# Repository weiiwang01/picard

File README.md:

# PiCard

> [!IMPORTANT]  
> PiCard is currently under development.

PiCard is a miniaturized Raspberry Pi Compute Module carrier board optimized for Linux server use cases.

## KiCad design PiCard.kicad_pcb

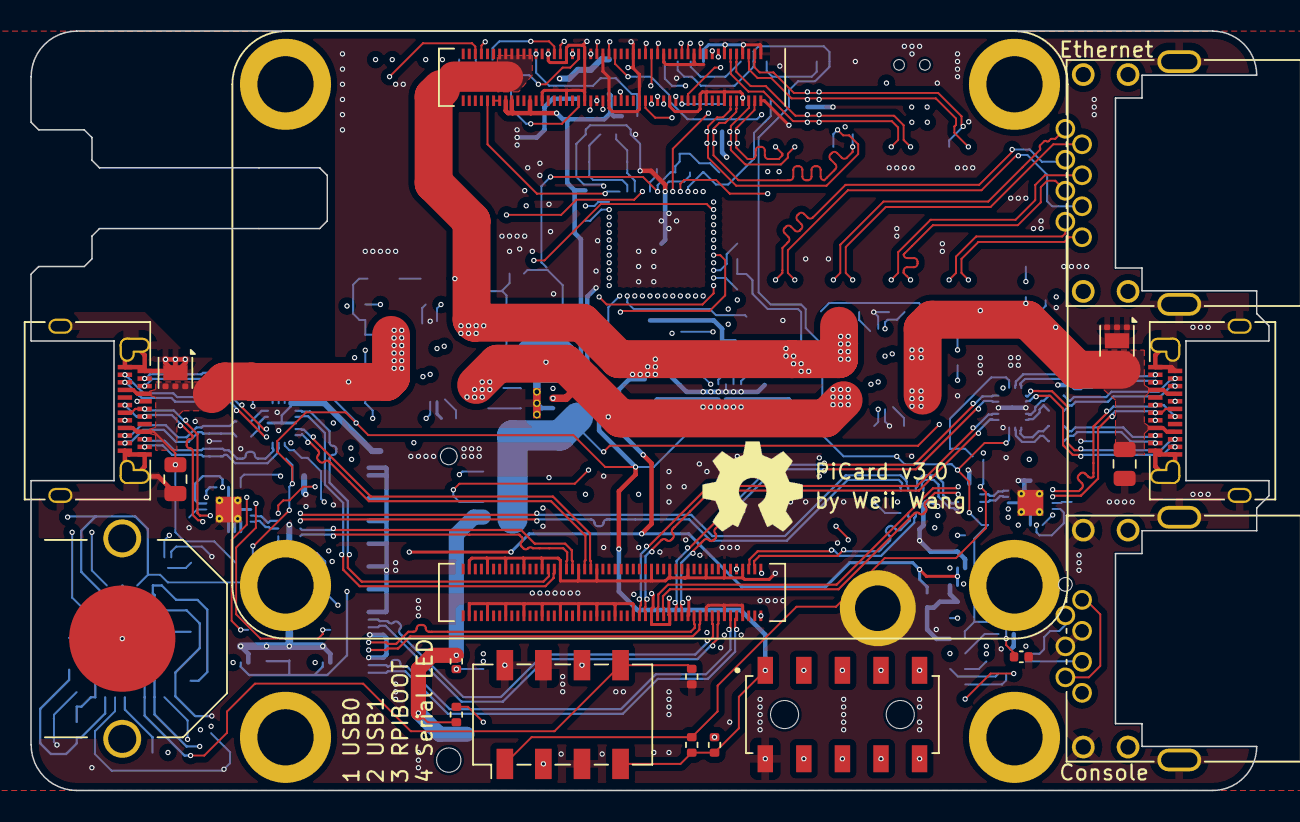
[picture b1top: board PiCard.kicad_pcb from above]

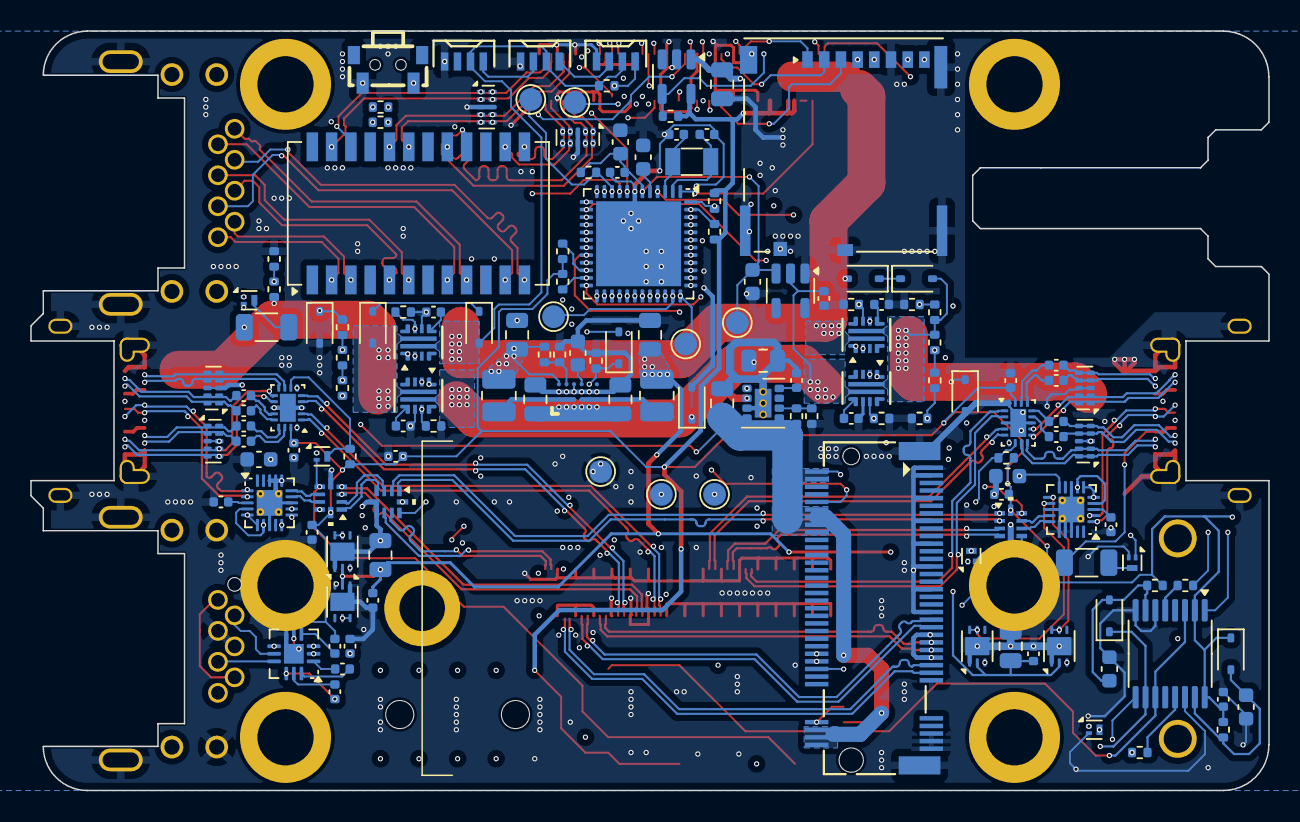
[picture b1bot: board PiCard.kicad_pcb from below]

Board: 6 copper layers, 81.5 x 50.0 mm, 166 parts (145 on the bottom side), 201 nets.

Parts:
BT1: CR1220 Battery; BAT-SMD_MY-1220-03
C1, C2, C3, C4, C5, C17, C21, C27, C28, C29, C30, C31, C32, C33, C34, C35, C36, C37, C38, C39, C40, C41, C43, C46, C51: 100n; C_0402_1005Metric
C6, C7, C25, C26, C44, C47: 1u; C_0603_1608Metric
C8, C18, C22: 10u; C_0805_2012Metric
C9, C10, C13, C14: 22u; C_0805_2012Metric
C11, C12: 47u; C_0805_2012Metric
C15: 22n; C_0603_1608Metric
C16: 430pF; C_0402_1005Metric
C19, C20, C23, C24: 2.2n; C_0402_1005Metric
C42: 4.7u; C_0603_1608Metric
C45, C48: 18pf; C_0402_1005Metric
C49, C50: 4.7u 50V; C_0805_2012Metric
ComputeModule1: ComputeModule4-CM4; Raspberry-Pi-4-Compute-Module
D1, D2, D3, D8, D9: 1N5819WS; D_SOD-323
D4, D7: Zener 20V; D_SOD-323
D5, D6, D13: D; D_SOD-323
D10, D11, D12: WS2812B; LED-SMD_4P-L4.0-W1.7-R
H1, H2: MountingHole; MOUNTING-HOLE
J1: RS232; RJ45-TH_RJ45-005-202-11
J2: Ethernet; RJ45-TH_RJ45-005-202-11
J3: Micro_SD_Card_Det2; SDCARD_MOLEX_503398-1892
J4: Bus_M.2_Socket_M; CONN-SMD_APCI0146-P001A
J5, J6: USB_C_Receptacle; USB-C-SMD_TYPE-C-31-M-27
J7: Conn_02x05_Odd_Even; HARWIN_M20-7810545R
L1, L2: 1u; L_1008_2520Metric
Q1, Q2, Q3, Q4, Q5: DMN32D2LFB4; Diodes_DFN1006-3
R1, R2, R5, R6: 470; R_0402_1005Metric
R3, R4, R12: 100k 1%; R_0402_1005Metric
R7, R8, R14, R25, R26, R39, R40, R41: 12k; R_0402_1005Metric
R9, R34, R35, R37, R38: 3.3k; R_0402_1005Metric
R10: 787k; R_0402_1005Metric
R11: 309k; R_0402_1005Metric
R13: 150k 1%; R_0402_1005Metric
R15, R16: 220k 1%; R_0402_1005Metric
R17, R18: 59k; R_0402_1005Metric
R19, R20: 28.7k; R_0402_1005Metric
R21, R22, R23, R24: 953; R_0402_1005Metric
R27, R28: 120k; R_0402_1005Metric
R29, R30: 4.7k 0.25W; R_1206_3216Metric
R31, R32: 10k; R_0402_1005Metric
R33, R36: 5.1k; R_0402_1005Metric
SW1: SW_Push; SW-SMD_L4.7-W3.5-P3.35-EH
SW2: SW_DIP_x04; SW-SMD_8P-L11.1-W6.2-P2.54-LS7.8
SYM1: PiCard v3.0; PICARD_NAMEPLATE
TP1, TP2, TP3, TP4, TP5, TP6, TP7, TP8: TestPoint; TestPoint_Pad_D1.5mm
TR1: H2456G; XFMR-SMD-24_L16.6-W9.0-LS9.6-BL
U1: ADM3101EACPZ; LFCSP-12-1EP_3x3mm_P0.5mm_EP1.3x1.3mm
U2: 74HC123PW; TSSOP-16_4.4x5mm_P0.65mm
U3, U4, U18, U19, U20, U21: TPD4EUSB30; USON-10_2.5x1.0mm_P0.5mm
U5: AP2191W; SOT-23-5
U6: TPS82130; Texas_SIL0008D_MicroSiP-8-1EP_2.8x3mm_P0.65mm_EP1.1x1.9mm_T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
U7: TPS62180; YZF0024AMAM
U8, U13, U14, U15: AP21510; DFN-6-1EP_2x1.8mm_P0.5mm_EP1.2x1.6mm
U9, U10: TVS2200DRV; WSON-6-1EP_2x2mm_P0.65mm_EP1x1.6mm
U11, U12, U16, U17: TPS259470; RPW0010A-MFG
U22, U23: TPD6S300A; WQFN-20-1EP_3x3mm_P0.4mm_EP1.7x1.7mm_ThermalVias
U24, U25: FUSB340TMX; QFN-18-1EP_2x2.8mm_P0.4mm_EP1.05x1.85mm
U26, U27, U28: TS3USB221; RSE10
U29: TLV70433; SOT-23-5
U30: STM32G071CBUx; QFN-48-1EP_7x7mm_P0.5mm_EP5.6x5.6mm
Y1: 32.768kHz; Crystal_SMD_3215-2Pin_3.2x1.5mm

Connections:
+3.3V: C2.1, C5.2, C29.2, C30.2, C39.2, C40.2, C41.2, C51.1, ComputeModule1.78 (GPIO_VREF(1.8v/3.3v_Input)), ComputeModule1.84 (+3.3v_(Output)), ComputeModule1.86 (+3.3v_(Output)), D1.1 (K), D2.1 (K), J2.10, J2.12, J7.1, R3.1, R4.1, R7.2, R25.1, R26.1, R34.2, R35.2, R37.2, R38.2, R39.1, R40.1, SW2.4, U1.5 (VCC), U2.2 (B), U2.10 (B), U2.16 (VCC), U5.5 (IN), U24.17 (VDD), U25.17 (VDD), U26.10 (VCC), U27.10 (VCC), U28.10 (VCC)
+5V: C11.1, C12.1, C17.1, C18.1, C21.1, C22.1, ComputeModule1.77 (+5v_(Input)), ComputeModule1.79 (+5v_(Input)), ComputeModule1.81 (+5v_(Input)), ComputeModule1.83 (+5v_(Input)), ComputeModule1.85 (+5v_(Input)), ComputeModule1.87 (+5v_(Input)), D4.2 (A), D7.2 (A), D10.2 (VDD), D11.2 (VDD), D12.2 (VDD), L1.2, L2.2, R10.1, R33.1, U7.A4 (VO), U8.2 (IN), U13.2 (IN), U14.2 (IN), U15.2 (IN), U16.5 (IN), U17.5 (IN)
/MCU/LDO_3.3V: C42.1, C43.2, C47.1, R36.2, TP4.1, U29.3 (OUT), U30.6 (VDD)
/MCU/MCU_BUTTON: SW1.2, U30.9 (PF1)
/MCU/WS2812_DIN: D10.1 (DIN), R33.2, U30.12 (PA1)
/Module A/DA_N: J2.2, TR1.8 (MX3+)
/Module A/DA_P: J2.1, TR1.9 (MX3-)
/Module A/DB_N: J2.6, TR1.11 (MX4+)
/Module A/DB_P: J2.3, TR1.12 (MX4-)
/Module A/DC_N: J2.5, TR1.5 (MX2+)
/Module A/DC_P: J2.4, TR1.6 (MX2-)
/Module A/DD_N: J2.8, TR1.2 (MX1+)
/Module A/DD_P: J2.7, TR1.3 (MX1-)
/Module A/ETH_LEDG: ComputeModule1.17 (Ethernet_nLED2(3.3v)), R5.2
/Module A/ETH_LEDY: ComputeModule1.15 (Ethernet_nLED3(3.3v)), R6.2
/Module A/GPIO14_UART_TX: ComputeModule1.55 (GPIO14), U1.3 (TIN), U2.1 (A)
/Module A/GPIO15_UART_RX: ComputeModule1.51 (GPIO15), U1.2 (ROUT), U2.9 (A)
/Module A/RS232_RXD: J1.6, U1.9 (RIN)
/Module A/RS232_TXD: J1.3, U1.8 (TOUT)
/Module A/SD_CLK: ComputeModule1.57 (SD_CLK), J3.5 (CLK)
/Module A/SD_CMD: ComputeModule1.62 (SD_CMD), J3.3 (CMD)
/Module A/SD_DAT0: ComputeModule1.63 (SD_DAT0), J3.7 (DAT0)
/Module A/SD_DAT1: ComputeModule1.67 (SD_DAT1), J3.8 (DAT1)
/Module A/SD_DAT2: ComputeModule1.69 (SD_DAT2), J3.1 (DAT2)
/Module A/SD_DAT3: ComputeModule1.61 (SD_DAT3), J3.2 (DAT3/CD)
/Module A/SD_PWR: C8.1, J3.4 (VDD), U5.1 (OUT)
/Module A/SD_PWR_ON: ComputeModule1.75 (SD_PWR_ON), R7.1, U5.4 (EN)
/Module A/TRD0_N: ComputeModule1.10 (Ethernet_Pair0_N), TR1.17, U4.2 (D1-), U4.9 (NC)
/Module A/TRD0_P: ComputeModule1.12 (Ethernet_Pair0_P), TR1.16 (TD3-), U4.1 (D1+), U4.10 (NC)
/Module A/TRD1_N: ComputeModule1.6 (Ethernet_Pair1_N), TR1.14 (TD4+), U4.4 (D2+), U4.7 (NC)
/Module A/TRD1_P: ComputeModule1.4 (Ethernet_Pair1_P), TR1.13 (TD4-), U4.5 (D2-), U4.6 (NC)
/Module A/TRD2_N: ComputeModule1.9 (Ethernet_Pair2_N), TR1.20 (TD2+), U3.4 (D2+), U3.7 (NC)
/Module A/TRD2_P: ComputeModule1.11 (Ethernet_Pair2_P), TR1.19 (TD2-), U3.5 (D2-), U3.6 (NC)
/Module A/TRD3_N: ComputeModule1.5 (Ethernet_Pair3_N), TR1.23 (TD1+), U3.2 (D1-), U3.9 (NC)
/Module A/TRD3_P: ComputeModule1.3 (Ethernet_Pair3_P), TR1.22 (TD1-), U3.1 (D1+), U3.10 (NC)
/Module A/UART_RX_ACT: R2.1, U2.5 (Q)
/Module A/UART_TX_ACT: R1.2, U2.13 (Q)
/Module B/PCIE_CLK_N: ComputeModule1.112 (PCIe_CLK_N), J4.53 (REFCLKn)
/Module B/PCIE_CLK_P: ComputeModule1.110 (PCIe_CLK_P), J4.55 (REFCLKp)
/Module B/PCIE_CLK_nREQ: ComputeModule1.102 (PCIe_nCLKREQ), J4.52 (~CLKREQ)
/Module B/PCIE_RX_N: ComputeModule1.118 (PCIe_RX_N), J4.41 (PERn0/SATA-B+)
/Module B/PCIE_RX_P: ComputeModule1.116 (PCIe_RX_P), J4.43 (PERp0/SATA-B-)
/Module B/PCIE_TX_N: ComputeModule1.124 (PCIe_TX_N), J4.47 (PETn0/SATA-A-)
/Module B/PCIE_TX_P: ComputeModule1.122 (PCIe_TX_P), J4.49 (PETp0/SATA-A+)
/Module B/PCIE_nRST: ComputeModule1.109 (PCIe_nRST), J4.50 (~PERST)
/USB/MUX0_TX1+: C34.2, U25.16 (SSTX1-)
/USB/MUX0_TX1-: C32.2, U25.15 (SSTX1+)
/USB/MUX0_TX2+: C38.2, U25.14 (SSTX2-)
/USB/MUX0_TX2-: C36.2, U25.13 (SSTX2+)
/USB/MUX1_TX1+: C33.2, U24.16 (SSTX1-)
/USB/MUX1_TX1-: C31.2, U24.15 (SSTX1+)
/USB/MUX1_TX2+: C37.2, U24.13 (SSTX2+)
/USB/MUX1_TX2-: C35.2, U24.14 (SSTX2-)
/USB/MUX_USB0_HS_D+: U27.4 (2D-), U28.1 (1D+)
/USB/MUX_USB0_HS_D-: U27.3 (2D+), U28.2 (1D-)
/USB/MUX_USB1_HS_D+: U26.1 (1D+), U27.2 (1D-)
/USB/MUX_USB1_HS_D-: U26.2 (1D-), U27.1 (1D+)
/USB/USB0_CC1: J6.A5 (CC1), U22.4 (C_CC1), U22.7 (RPD_G1)
/USB/USB0_CC2: J6.B5 (CC2), U22.5 (C_CC2), U22.6 (RPD_G2)
/USB/USB0_DN: J6.A7 (D-), J6.B7 (D-), U22.1 (C_SBU1)
/USB/USB0_DP: J6.A6 (D+), J6.B6 (D+), U22.2 (C_SBU2)
/USB/USB0_HS_D+: U22.14 (SBU2), U28.8 (D+)
/USB/USB0_HS_D-: U22.15 (SBU1), U28.7 (D-)
/USB/USB0_SS_RX1+: J6.B11 (RX1+), U18.5 (D2-), U18.6 (NC), U25.11 (SSRX1-)
/USB/USB0_SS_RX1-: J6.B10 (RX1-), U18.4 (D2+), U18.7 (NC), U25.10 (SSRX1+)
/USB/USB0_SS_RX2+: J6.A11 (RX2+), U21.5 (D2-), U21.6 (NC), U25.8 (SSRX2+)
/USB/USB0_SS_RX2-: J6.A10 (RX2-), U21.4 (D2+), U21.7 (NC), U25.9 (SSRX2-)
/USB/USB0_SS_TX1+: C34.1, J6.A2 (TX1+), U18.2 (D1-), U18.9 (NC)
/USB/USB0_SS_TX1-: C32.1, J6.A3 (TX1-), U18.1 (D1+), U18.10 (NC)
/USB/USB0_SS_TX2+: C36.1, J6.B2 (TX2+), U21.2 (D1-), U21.9 (NC)
/USB/USB0_SS_TX2-: C38.1, J6.B3 (TX2-), U21.1 (D1+), U21.10 (NC)
/USB/USB1_CC1: J5.A5 (CC1), U23.4 (C_CC1), U23.7 (RPD_G1)
/USB/USB1_CC2: J5.B5 (CC2), U23.5 (C_CC2), U23.6 (RPD_G2)
/USB/USB1_DN: J5.A7 (D-), J5.B7 (D-), U23.1 (C_SBU1)
/USB/USB1_DP: J5.A6 (D+), J5.B6 (D+), U23.2 (C_SBU2)
/USB/USB1_HS_D+: U23.14 (SBU2), U26.8 (D+)
/USB/USB1_HS_D-: U23.15 (SBU1), U26.7 (D-)
/USB/USB1_SS_RX1+: J5.B11 (RX1+), U19.2 (D1-), U19.9 (NC), U24.11 (SSRX1-)
/USB/USB1_SS_RX1-: J5.B10 (RX1-), U19.1 (D1+), U19.10 (NC), U24.10 (SSRX1+)
/USB/USB1_SS_RX2+: J5.A11 (RX2+), U20.1 (D1+), U20.10 (NC), U24.8 (SSRX2+)
/USB/USB1_SS_RX2-: J5.A10 (RX2-), U20.2 (D1-), U20.9 (NC), U24.9 (SSRX2-)
/USB/USB1_SS_TX1+: C33.1, J5.A2 (TX1+), U19.5 (D2-), U19.6 (NC)
/USB/USB1_SS_TX1-: C31.1, J5.A3 (TX1-), U19.4 (D2+), U19.7 (NC)
/USB/USB1_SS_TX2+: C37.1, J5.B2 (TX2+), U20.4 (D2+), U20.7 (NC)
/USB/USB1_SS_TX2-: C35.1, J5.B3 (TX2-), U20.5 (D2-), U20.6 (NC)
/USB/~USB0_SS_EN: Q5.3 (D), R40.2, U25.7 (~OE)
/USB/~USB1_SS_EN: Q4.3 (D), R39.2, U24.7 (~OE)
CM_ACT_LED: ComputeModule1.21 (LED_nACT), U30.8 (PF0)
CM_I2C1_SCL: ComputeModule1.56 (GPIO3), R34.1, TP6.1, U30.47 (PB8)
CM_I2C1_SDA: ComputeModule1.58 (GPIO2), R35.1, TP7.1, U30.48 (PB9)
CM_I2C2_SCL: ComputeModule1.34 (GPIO5), J7.3
CM_I2C2_SDA: ComputeModule1.54 (GPIO4), J7.4
CM_ID_SC: ComputeModule1.35 (ID_SC), R37.1, U30.22 (PB10)
CM_ID_SD: ComputeModule1.36 (ID_SD), R38.1, U30.23 (PB11)
CM_PWR_BUTTON: ComputeModule1.92 (PWR_BUT), U30.1 (PC13)
CM_PWR_EN: ComputeModule1.48 (GPIO27), D13.2 (A)
CM_PWR_LED: ComputeModule1.95 (LED_nPWR), U30.46 (PB7)
CM_SPI1_CSN0: ComputeModule1.49 (GPIO18), J7.10
CM_SPI1_SCLK: ComputeModule1.25 (GPIO21), J7.7
CM_SPI1_SIO0: ComputeModule1.27 (GPIO20), J7.8
CM_SPI1_SIO1: ComputeModule1.26 (GPIO19), J7.9
CM_UART3_RX: ComputeModule1.40 (GPIO9), J7.6
CM_UART3_TX: ComputeModule1.39 (GPIO8), J7.5
CM_UART4_RX: ComputeModule1.28 (GPIO13), TP5.1, U30.11 (PA0)
CM_USB2_D+: ComputeModule1.105 (USB2_P), U27.7 (D-)
CM_USB2_D-: ComputeModule1.103 (USB2_N), U27.8 (D+)
CM_USB2_MUX_SEL: U27.9 (S), U30.34 (PA10/PA12)
CM_USB3_0_HS_D+: ComputeModule1.134 (USB3-0-D_P), U28.3 (2D+)
CM_USB3_0_HS_D-: ComputeModule1.136 (USB3-0-D_N), U28.4 (2D-)
CM_USB3_0_SS_RX+: ComputeModule1.130 (USB3-0-RX_P), U25.5 (SSRXCOM+)
CM_USB3_0_SS_RX-: ComputeModule1.128 (USB3-0-RX_N), U25.4 (SSRXCOM-)
CM_USB3_0_SS_TX+: ComputeModule1.142 (USB3-0-TX_P), U25.2 (SSTXCOM+)
CM_USB3_0_SS_TX-: ComputeModule1.140 (USB3-0-TX_N), U25.1 (SSTXCOM-)
CM_USB3_1_HS_D+: ComputeModule1.163 (USB3-1-D_P), U26.3 (2D+)
CM_USB3_1_HS_D-: ComputeModule1.165 (USB3-1-D_N), U26.4 (2D-)
CM_USB3_1_SS_RX+: ComputeModule1.159 (USB3-1-RX_P), U24.5 (SSRXCOM+)
CM_USB3_1_SS_RX-: ComputeModule1.157 (USB3-1-RX_N), U24.4 (SSRXCOM-)
CM_USB3_1_SS_TX+: ComputeModule1.169 (USB3-1-TX_N), U24.2 (SSTXCOM+)
CM_USB3_1_SS_TX-: ComputeModule1.171 (USB3-1-TX_P), U24.1 (SSTXCOM-)
CM_USB_OTG_ID: ComputeModule1.101 (USB_OTG_ID), U30.39 (PD1)
GND: C3.2, C5.1, C6.2, C7.2, C8.2, C9.2, C10.2, C11.2, C12.2, C13.2, C14.2, C15.2, C16.1, C17.2, C18.2, C19.2, C20.2, C21.2, C22.2, C23.2, C24.2, C25.1, C26.1, C27.2, C28.1, C29.1, C30.1, C39.1, C40.1, C41.1, C42.2, C43.1, C44.1, C45.1, C46.1, C47.2, C48.1, C49.1, C50.1, C51.2, ComputeModule1.1 (GND), ComputeModule1.2 (GND), ComputeModule1.7 (GND), ComputeModule1.8 (GND), ComputeModule1.13 (GND), ComputeModule1.14 (GND), ComputeModule1.20 (EEPROM_nWP), ComputeModule1.22 (GND), ComputeModule1.23 (GND), ComputeModule1.32 (GND), ComputeModule1.33 (GND), ComputeModule1.42 (GND), ComputeModule1.43 (GND), ComputeModule1.52 (GND), ComputeModule1.53 (GND), ComputeModule1.59 (GND), ComputeModule1.60 (GND), ComputeModule1.65 (GND), ComputeModule1.66 (GND), ComputeModule1.71 (GND), ComputeModule1.74 (GND), ComputeModule1.107 (GND), ComputeModule1.108 (GND), ComputeModule1.113 (GND), ComputeModule1.114 (GND), ComputeModule1.119 (GND), ComputeModule1.120 (GND), ComputeModule1.125 (GND), ComputeModule1.126 (GND), ComputeModule1.131 (GND), ComputeModule1.132 (GND), ComputeModule1.137 (GND), ComputeModule1.138 (GND), ComputeModule1.144 (GND), ComputeModule1.150 (GND), ComputeModule1.155 (GND), ComputeModule1.156 (GND), ComputeModule1.161 (GND), ComputeModule1.162 (GND), ComputeModule1.167 (GND), ComputeModule1.168 (GND), ComputeModule1.173 (GND), ComputeModule1.174 (GND), ComputeModule1.179 (GND), ComputeModule1.180 (GND), ComputeModule1.185 (GND), ComputeModule1.186 (GND), ComputeModule1.191 (GND), ComputeModule1.192 (GND), ComputeModule1.197 (GND), ComputeModule1.198 (GND), D3.2 (A), D8.2 (A), D9.2 (A), D10.4 (VSS), D11.4 (VSS), D12.4 (VSS), J1.4, J1.5, J1.9, J1.11, J1.SH, J2.SH, J3.6 (VSS), J3.9 (DET_B), J3.10 (DET_A), J3.11 (SHIELD), J4.1 (GND), J4.3 (GND), J4.9 (GND), J4.15 (GND), J4.21 (GND), J4.27 (GND), J4.33 (GND), J4.39 (GND), J4.45 (GND), J4.51 (GND), J4.57 (GND), J4.71 (GND), J4.73 (GND), J4.75 (GND), J5.A1 (GND), J5.A12 (GND), J5.B1 (GND), J5.B12 (GND), J5.S1 (SHIELD), J6.A1 (GND), J6.A12 (GND), J6.B1 (GND), J6.B12 (GND), J6.S1 (SHIELD), J7.2, Q1.2 (S), Q2.2 (S), Q3.2 (S), R12.1, R13.2, R14.2, R19.2, R20.2, R21.2, R22.2, R23.2, R24.2, R31.2, R32.2, R41.2, SW1.1, SW2.3, SW2.7, SW2.8, TP8.1, U1.6 (GND), U1.13 (GND), U2.6 (Cext), U2.8 (GND), U2.14 (Cext), U3.3 (GND), U3.8 (GND), U4.3 (GND), U4.8 (GND), U5.2 (GND), U6.3 (GND), U6.9 (GND), U7.A3 (GND), U7.B3 (GND), U7.C3 (GND), U7.C4 (GND), U7.D3 (GND), U7.E3 (GND), U7.F3 (GND), U8.1 (GND), U8.7 (GND), U9.1 (GND), U9.2 (GND), U9.3 (GND), U9.7 (GND), U10.1 (GND), U10.2 (GND), U10.3 (GND), U10.7 (GND), U11.8 (GND), U12.8 (GND), U13.1 (GND), U13.7 (GND), U14.1 (GND), U14.7 (GND), U15.1 (GND), U15.7 (GND), U16.8 (GND), U17.8 (GND), U18.3 (GND), U18.8 (GND), U19.3 (GND), U19.8 (GND), U20.3 (GND), U20.8 (GND), U21.3 (GND), U21.8 (GND), U22.8 (GND), U22.13 (GND), U22.16 (GND), U22.17 (GND), U22.18 (GND), U22.21 (GND), U23.8 (GND), U23.13 (GND), U23.16 (GND), U23.17 (GND), U23.18 (GND), U23.21 (GND), U24.3 (GND), U24.12 (GND__1), U24.18 (GND__2), U24.19 (EP), U25.3 (GND), U25.12 (GND__1), U25.18 (GND__2), U25.19 (EP), U26.5 (GND), U27.5 (GND), U27.6 (~OE), U28.5 (GND), U29.1 (GND), U30.7 (VSS), U30.49 (VSS)
M2_3.3V: C14.1, C25.2, C26.2, J4.2 (3.3V), J4.4 (3.3V), J4.12 (3.3V), J4.14 (3.3V), J4.16 (3.3V), J4.18 (3.3V), J4.70 (3.3V), J4.72 (3.3V), J4.74 (3.3V), R8.2, R9.2, R11.1, U6.4 (VOUT), U6.5 (VOUT), U22.10 (VPWR), U23.10 (VPWR)
M2_LED: J4.10 (DAS/~DSS/~LED1), U30.42 (PB3)
M2_SUSCLK: J4.68 (SUSCLK), R9.1, U30.29 (PA9/UCPD1_DBCC1)
MCU_SWDCLK: ComputeModule1.30 (GPIO6), TP3.1, U30.36 (PA14)
MCU_SWDIO: ComputeModule1.37 (GPIO7), TP2.1, U30.35 (PA13)
MCU_nRST: ComputeModule1.38 (GPIO11), R36.1, TP1.1, U30.10 (PF2)
unnamed: BT1.1 (+), Q3.1 (G), U30.4 (VBAT)
unnamed: BT1.2 (-), Q3.3 (D)
unnamed: ComputeModule1.88 (+1.8v_(Output)), ComputeModule1.90 (+1.8v_(Output))
unnamed: C7.1, D1.2 (A), R4.2, U2.15 (RCext)
unnamed: C6.1, D2.2 (A), R3.2, U2.7 (RCext)
unnamed: D4.1 (K), D5.1 (K)
unnamed: D6.1 (K), D7.1 (K)
unnamed: D10.3 (DOUT), D11.1 (DIN)
unnamed: D11.3 (DOUT), D12.1 (DIN)
unnamed: J1.2, J1.7
unnamed: J1.10, R2.2
unnamed: J1.12, R1.1
unnamed: J2.9, R6.1
unnamed: J2.11, R5.1
unnamed: J4.54 (~PEWAKE), R8.1
unnamed: L1.1, U7.A2 (SW1), U7.B2 (SW1), U7.C2 (SW1)
unnamed: L2.1, U7.D2 (SW2), U7.E2 (SW2), U7.F2 (SW2)
unnamed: Q1.3 (D), R29.2
unnamed: Q2.3 (D), R30.2
unnamed: C1.1, U1.1 (C1+)
unnamed: C1.2, U1.12 (C1-)
unnamed: C4.1, U1.11 (C2+)
unnamed: C4.2, U1.10 (C2-)
unnamed: C2.2, U1.4 (V+)
unnamed: C3.1, U1.7 (V-)
unnamed: R11.2, R12.2, U6.6 (FB)
unnamed: C16.2, U6.8 (SS/TR)
unnamed: R10.2, R13.1, U7.B4 (FB)
unnamed: C15.1, U7.D4 (SS)
unnamed: R15.2, R17.1, U11.1 (EN/UVLO)
unnamed: R17.2, R19.1, U11.2 (OVLO)
unnamed: C19.1, U11.7 (dVdt)
unnamed: R16.2, R18.1, U12.1 (EN/UVLO)
unnamed: R18.2, R20.1, U12.2 (OVLO)
unnamed: C20.1, U12.7 (dVdt)
unnamed: C23.1, U16.7 (dVdt)
unnamed: C24.1, U17.7 (dVdt)
unnamed: C27.1, U22.3 (VBIAS)
unnamed: C28.2, U23.3 (VBIAS)
unnamed: C45.2, U30.2 (PC14), Y1.2
unnamed: C48.2, U30.3 (PC15), Y1.1
unnamed: C44.2, U30.5 (VREF+)
PWR_EN: D13.1 (K), R14.1, U6.1 (EN), U7.E4 (EN), U30.37 (PA15)
RPIBOOT: ComputeModule1.93 (nRPIBOOT), SW2.6
UART_ACT_EN: R41.1, SW2.5, U2.3 (Clr), U2.11 (Clr)
UCPD1_CC1: U8.5 (OUT), U8.6 (OUT), U22.12 (CC1), U30.28 (PA8)
UCPD1_CC1_VCONN_EN: U8.3 (EN), U30.26 (PB14)
UCPD1_CC2: U13.5 (OUT), U13.6 (OUT), U22.11 (CC2), U30.27 (PB15)
UCPD1_CC2_VCONN_EN: U13.3 (EN), U30.25 (PB13)
UCPD2_CC1: U14.5 (OUT), U14.6 (OUT), U23.12 (CC1), U30.38 (PD0)
UCPD2_CC1_VCONN_EN: U14.3 (EN), U30.30 (PC6)
UCPD2_CC2: U15.5 (OUT), U15.6 (OUT), U23.11 (CC2), U30.40 (PD2)
UCPD2_CC2_VCONN_EN: U15.3 (EN), U30.31 (PC7)
USB0_DISCHARGE: Q2.1 (G), U30.16 (PA5)
USB0_HS_MUX_SEL: Q5.1 (G), U28.9 (S), U30.43 (PB4)
USB0_SINK_ILM: R22.1, U12.9 (ILM), U30.13 (PA2)
USB0_SRC_EN: U17.1 (EN/UVLO), U30.18 (PA7)
USB0_SRC_ILM: R24.1, U17.9 (ILM), U30.21 (PB2)
USB0_SRC_OVLO: U17.2 (OVLO), U30.19 (PB0)
USB0_SS_MUX_SEL: U25.6 (S), U30.17 (PA6)
USB0_VBUS: C50.2, D5.2 (A), D8.1 (K), J6.A4 (VBUS), J6.A9 (VBUS), J6.B4 (VBUS), J6.B9 (VBUS), R16.1, R28.1, R30.1, U10.4 (IN), U10.5 (IN), U10.6 (IN), U12.5 (IN), U17.6 (OUT)
USB0_VSENS: R28.2, R32.1, U30.15 (PA4)
USB1_DISCHARGE: Q1.1 (G), U30.33 (PA9/PA11)
USB1_HS_MUX_SEL: Q4.1 (G), U26.9 (S), U30.32 (PA10/UCPD1_DBCC2)
USB1_SINK_ILM: R21.1, U11.9 (ILM), U30.24 (PB12)
USB1_SRC_EN: U16.1 (EN/UVLO), U30.45 (PB6)
USB1_SRC_ILM: R23.1, U16.9 (ILM), U30.14 (PA3)
USB1_SRC_OVLO: U16.2 (OVLO), U30.44 (PB5)
USB1_SS_MUX_SEL: U24.6 (S), U30.41 (PD3)
USB1_VBUS: C49.2, D6.2 (A), D9.1 (K), J5.A4 (VBUS), J5.A9 (VBUS), J5.B4 (VBUS), J5.B9 (VBUS), R15.1, R27.1, R29.1, U9.4 (IN), U9.5 (IN), U9.6 (IN), U11.5 (IN), U16.6 (OUT)
USB1_VSENS: R27.2, R31.1, U30.20 (PB1)
VBUS: C9.1, C10.1, C13.1, C46.2, D3.1 (K), U6.2 (VIN), U7.A1 (VIN1), U7.B1 (VIN1), U7.C1 (VIN1), U7.D1 (VIN2), U7.E1 (VIN2), U7.F1 (VIN2), U11.6 (OUT), U12.6 (OUT), U29.2 (IN)
~USB0_USB_EN: Q5.2 (S), R26.2, SW2.1, U28.6 (~OE)
~USB1_USB_EN: Q4.2 (S), R25.2, SW2.2, U26.6 (~OE)

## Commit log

2024-04-18 First prototype
2024-04-26 Fix ethernet wiring order
2024-05-11 Clean up schematics
2024-05-11 Upload case design
2024-11-02 PiCard v2
2024-11-12 Upload enclosure design for PiCard v2
2024-12-30 PiCard v2.2
2025-02-23 wip2
2025-03-30 wip3
2025-05-12 final v3.0
2025-05-19 PiCard v3.0
